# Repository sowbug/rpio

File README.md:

RPio: A Raspberry Pi Breakout Board
===========================================

In an effort to help intrepid hackers who hook their brand-new Raspberry Pi's GPIO pins to standard 5-volt maker fare and wonder why their boards stop working, we present RPio, which does the following:

  * Shifts the voltage of 15 of the 17 GPIO pins from 3.3 to a user-selectable voltage (typically 5.0), and back again from the user-selected voltage to a safe 3.3V for the Raspberry Pi. In technical terms, this is *bidirectional level translation*. For the remaining two, pulls up in an I2C-compatible fashion.
  * Provides up to 150mA of 3.3-volt power, which is significantly more than the 50mA of 3.3v power provided by the GPIO pins. It's not enough to drive a robot up a hill, but it is enough to safely power a few ICs while writing data to an SD card.
  * Includes five current-limited LEDs, two for status and three for experimenting. One confirms that the board has been successfully connected to the Raspberry Pi. Another indicates that the level-shifted GPIO pins are live. The remaining three are cathode-grounded, anode-disconnected with headers ready to connect to GPIOs, for easy light-blinking fun.

Instructions
============

*These instructions are not yet tested. See Caveats below.*

These instructions will refer to the Raspberry Pi as the **RPi**. The breakout board is the **RPio**. The **north end** of the RPio is the end that has the 26-pin GPIO header matching the RPi's header. The **south end** is the other end. The RPi is assumed to be component-side up, with the SD card slot pointing left and the HDMI jack pointing down, toward you.

We're also assuming that you have already soldered either pin or socket headers to the GPIOs on your RPi, and soldered mating connectors to the RPio. The RPi reportedly won't ship with these GPIO pins soldered (except for the first batch of 2,000, which include male headers), so the kind that gets soldered on your board is a decision you get to make.

  1. Remove all shunts, jumper connectors, wires, etc., from the RPio.
  1. Turn off your RPi.
  1. Plug the RPio into the 26-pin GPIO header on the top of your RPi. This board should cover a little less than half of the top of your RPi in the east-west dimension, so that the south side of the board covers the RPi's SD receptacle. If you plug it in any other way, then both your boards will be destroyed, your home will burn down, your friends will stop calling, and your cat will leave you. See Caveats below.
  1. Turn on your RPi. You should see the LED on the RPio marked "CONNECTED" light up.
  1. Look at the small jumpers (IO-PWR-EXT and VTG-SEL) on the RPio. These two jumpers set the voltage for the I/O pins. If you need a weird voltage, such as 3.14159, then supply it yourself on IO-PWR-EXT, which is the two-pin header. Otherwise, pick 5V by connecting the two VTG-SEL pins labeled 5.0 and VIO, or else pick 3V by connecting VTG-SEL's 3.3 and VIO pins. If this is confusing, think of VIO as the part of the RPio waiting to be powered at the voltage you want, and the other numbered voltages on the RPio as potential sources for VIO; it's up to you to connect the right one and set VIO to the right voltage.
  1. If you've done the previous step correctly, then the IO-POWER LED should light up.
  1. If you need immediate gratification, find the LEDs on the south side of the RPio. Take a jumper wire and connect the header to the left of one of them to the pin marked GP0. Now [write some code](http://elinux.org/Rpi_Low-level_peripherals) on your RPi to enable that GPIO pin. The LED should light up.
  1. If you're wondering why you went through all this, get out a multimeter and measure the voltage of an enabled GPIO pin on the 26-pin header. It will be 3.3 volts. Now measure the same GPIO on the GP pinout of the RPio. Its voltage should match that of VIO. Moreover, when otherwise-incompatible voltages come into the RPio, they will be shifted safely to the 3.3 volts that the RPi needs. This last part is the important part: if you applied 5V to an RPi GPIO, the RPi would probably die. See Caveats below.
  1. Note that the pins marked SCL and SDA are special in that they're I2C compatible. They use a [MOSFET-based pullup](http://ics.nxp.com/support/documents/interface/pdf/an97055.pdf) that allows safe connection of external I2C lines at varying voltages. The compromise for this built-in pullup convenience is that these lines can't be used as GPIOs, but are largely dedicated to I2C functionality.

Caveats
=======

  * Messing with GPIOs is potentially dangerous to your Raspberry Pi, your possessions, and yourself. Please don't do it unless you know what you're doing and are willing to live with the consequences.

Credits
=======

  * Board design by [Mike Tsao](http://www.sowbug.com/) and [Dennis Gentry](https://github.com/dgentry).
  * Thanks to the [Adafruit Part Finder](http://www.ladyada.net/wiki/partfinder) for making us aware of the TXB0108.  [Datasheet here](http://www.ti.com/lit/ds/symlink/txb0108.pdf)

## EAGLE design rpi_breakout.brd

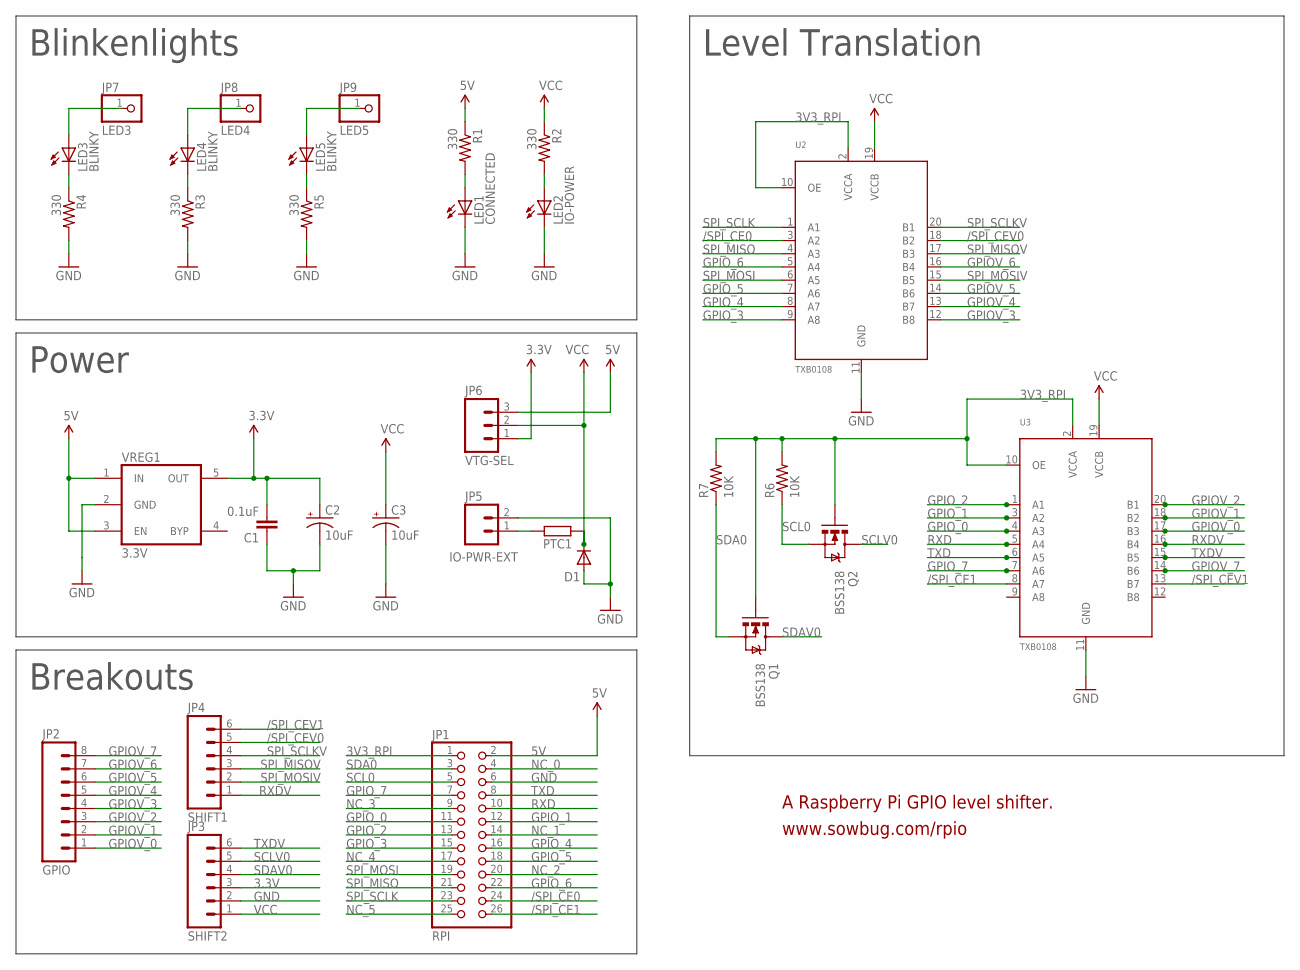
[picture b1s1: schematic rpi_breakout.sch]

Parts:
C1: 0.1uF; SPARKFUN_0805
C2, C3: 10uF; SPARKFUN_EIA3216
D1: SPARKFUN-DISCRETESEMI_DIODESOD; SPARKFUN-DISCRETESEMI_SOD-323
JP1: RPI; PINHEAD_2X13
JP2: GPIO; SPARKFUN_1X08_LOCK
JP3: SHIFT2; SPARKFUN_1X06_LOCK
JP4: SHIFT1; SPARKFUN_1X06_LOCK
JP5: IO-PWR-EXT; SPARKFUN_1X02_LOCK
JP6: VTG-SEL; SPARKFUN_1X03_LOCK
JP7: LED3; ADAFRUIT_1X01
JP8: LED4; ADAFRUIT_1X01
JP9: LED5; ADAFRUIT_1X01
LED1: CONNECTED; PROGRAMMER_CHIP-LED0805
LED2: IO-POWER; PROGRAMMER_CHIP-LED0805
LED3, LED4, LED5: BLINKY; PROGRAMMER_CHIP-LED0805
PTC1: RCL_R-EU_R1206; RCL_R1206
Q1, Q2: BSS138; SPARKFUN_SOT23-3
R1, R2, R3, R4, R5: 330; SPARKFUN_0805
R6, R7: 10K; SPARKFUN_0805
U2, U3: TXB0108; RPI_BREAKOUT_TSSOP20
VREG1: 3.3V; DP_DEVICES_SOT-23-5

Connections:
3.3V: C1.2, C2.A (+), JP3.3, JP6.1, VREG1.5 (OUT)
3V3_RPI: JP1.1, Q1.1 (G), Q2.1 (G), R6.2, R7.2, U2.2 (VCCA), U2.10 (OE), U3.2 (VCCA), U3.10 (OE)
5V: JP1.2, JP6.3, R1.1, VREG1.1 (IN), VREG1.3 (EN)
/SPI_CE0: JP1.24, U2.3 (A2)
/SPI_CE1: JP1.26, U3.8 (A7)
/SPI_CEV0: JP4.5, U2.18 (B2)
/SPI_CEV1: JP4.6, U3.13 (B7)
GND: C1.1, C2.C (-), C3.C (-), D1.2 (A), JP1.6, JP3.2, JP5.2, LED1.C, LED2.C, R3.2, R4.2, R5.2, U2.11 (GND), U3.11 (GND), VREG1.2 (GND)
GPIOV_0: JP2.1, U3.17 (B3)
GPIOV_1: JP2.2, U3.18 (B2)
GPIOV_2: JP2.3, U3.20 (B1)
GPIOV_3: JP2.4, U2.12 (B8)
GPIOV_4: JP2.5, U2.13 (B7)
GPIOV_5: JP2.6, U2.14 (B6)
GPIOV_6: JP2.7, U2.16 (B4)
GPIOV_7: JP2.8, U3.14 (B6)
GPIO_0: JP1.11, U3.4 (A3)
GPIO_1: JP1.12, U3.3 (A2)
GPIO_2: JP1.13, U3.1 (A1)
GPIO_3: JP1.15, U2.9 (A8)
GPIO_4: JP1.16, U2.8 (A7)
GPIO_5: JP1.18, U2.7 (A6)
GPIO_6: JP1.22, U2.5 (A4)
GPIO_7: JP1.7, U3.7 (A6)
LED3_JP: JP7.1, LED3.A
LED4_JP: JP8.1, LED4.A
LED5_JP1: JP9.1, LED5.A
unnamed: LED1.A, R1.2
unnamed: LED2.A, R2.2
unnamed: LED3.C, R4.1
unnamed: LED4.C, R3.1
unnamed: LED5.C, R5.1
NC_0: JP1.4
NC_1: JP1.14
NC_2: JP1.20
NC_3: JP1.9
NC_4: JP1.17
NC_5: JP1.25
RXD: JP1.10, U3.5 (A4)
RXDV: JP4.1, U3.16 (B4)
SCL0: JP1.5, Q2.2 (S), R6.1
SCLV0: JP3.5, Q2.3 (D)
SDA0: JP1.3, Q1.2 (S), R7.1
SDAV0: JP3.4, Q1.3 (D)
SPI_MISO: JP1.21, U2.4 (A3)
SPI_MISOV: JP4.3, U2.17 (B3)
SPI_MOSI: JP1.19, U2.6 (A5)
SPI_MOSIV: JP4.2, U2.15 (B5)
SPI_SCLK: JP1.23, U2.1 (A1)
SPI_SCLKV: JP4.4, U2.20 (B1)
TXD: JP1.8, U3.6 (A5)
TXDV: JP3.6, U3.15 (B5)
VCC: C3.A (+), D1.1 (C), JP3.1, JP6.2, PTC1.2, R2.1, U2.19 (VCCB), U3.19 (VCCB)
VCC_FUSE: JP5.1, PTC1.1

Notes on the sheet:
Breakouts
Power
Blinkenlights
Level Translation
A Raspberry Pi GPIO level shifter.
www.sowbug.com/rpio

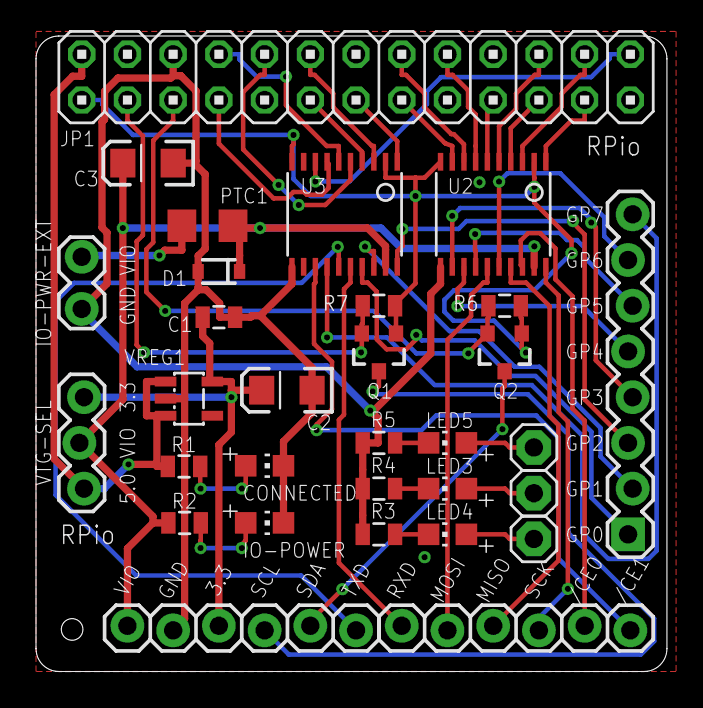
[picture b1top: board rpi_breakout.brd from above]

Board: 2 copper layers, 35.1 x 35.3 mm, 31 parts (0 on the bottom side), 48 nets.

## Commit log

2012-03-11 New.
2012-03-11 New README. Some labeling tweaks on the board.
2012-03-11 README nits.
2012-03-11 Rough route with 5 vias, some headers pulled inward
2012-03-11 Rotated GPIO pins, slightly tighter routing, 4 vias
2012-03-11 Smaller still. Power section moved S. Board size limited by two long headers. 3 vias.
2012-03-11 v0.0.2, restored polygons, fixed up silkscreen
2012-03-11 Updated README to make locations less specific.
2012-03-11 power/gnd and skinny net classes. mitered corners. better polygon isolation. 2 vias
2012-03-11 Moved 26 pin header NW. 7 vias.
2012-03-11 rpi_breakout -> RPio
2012-03-13 Split special-pin header into 2x6.
2012-03-13 Fixed jumper references.
2012-03-13 Beefed up everything, made board partial CC size
2012-03-13 Fatter still, handrouted, with funky Vcc polygons. Probably won't want to use this one.
2012-03-14 Smaller board footprint again; Merged from canton7's nice layout
2012-03-14 Restored labels for headers
2012-03-15 Moved left IC right for shorter traces
2012-03-15 Added solder jumper, RTC and diode protection, shortened traces (26.5 total)
2012-03-16 SCL/SDA pullup, 4.7K. GPIO labels are back.
2012-03-17 Moved pullup resistors near power.
2012-03-17 Line up the blinkenpins on a 0.1" grid
2012-03-17 Added polygons for 5V and 3.3V. Probably added a minor acid trap as well.
2012-03-17 Fixed acid trap, turned off display of bottom copper
2012-03-18 Fix schematic URL. Board PNG with pour.
2012-03-18 Crop.
2012-03-26 Added through-hole pull-up resistors. Rounded corners. Larger labels.
2012-03-26 Also: Swapped RX/TX and SDA/SCL for easier routing.
2012-03-26 New\! Improved\!
2012-03-26 Picture of the top
2012-03-26 New! Improved!
2012-03-28 Relaxed and shrank layout a bit. Added a blinkenlight.
2012-04-02 Interim checkin. Autorouter is SLOW today.
2012-04-02 A couple label touchups.
2012-04-03 Cleanup/routing after adding I2C-friendly level converter.
2012-04-13 Figured we ought to have common design rules
2012-04-17 Makefile conveniences.
2012-04-18 Updated for Seeed.
2012-04-22 Updated README for I2C.
2012-04-22 Missed one part about I2C. Fixed.
2012-12-11 Updated to reflect actual existence of RPs and added datasheet link.

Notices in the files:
parts and their libraries:
SparkFun: Licensing: CC v3.0 Share-Alike You are welcome to use this library for commercial purposes.
